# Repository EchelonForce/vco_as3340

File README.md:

# Eurorack VCO AS3340

This is a design for a eurorack VCO using the AS3340 VCO chip.

Full writeup here: https://www.robotdialogs.com/2023/02/eurorack-vco-module-as3340-v21.html
v1. writeup: https://www.robotdialogs.com/2022/09/eurorack-vco-module-as3340.html

This work is licensed under a Creative Commons Attribution-NonCommercial-ShareAlike 4.0 International License. https://creativecommons.org/licenses/by-nc-sa/4.0/

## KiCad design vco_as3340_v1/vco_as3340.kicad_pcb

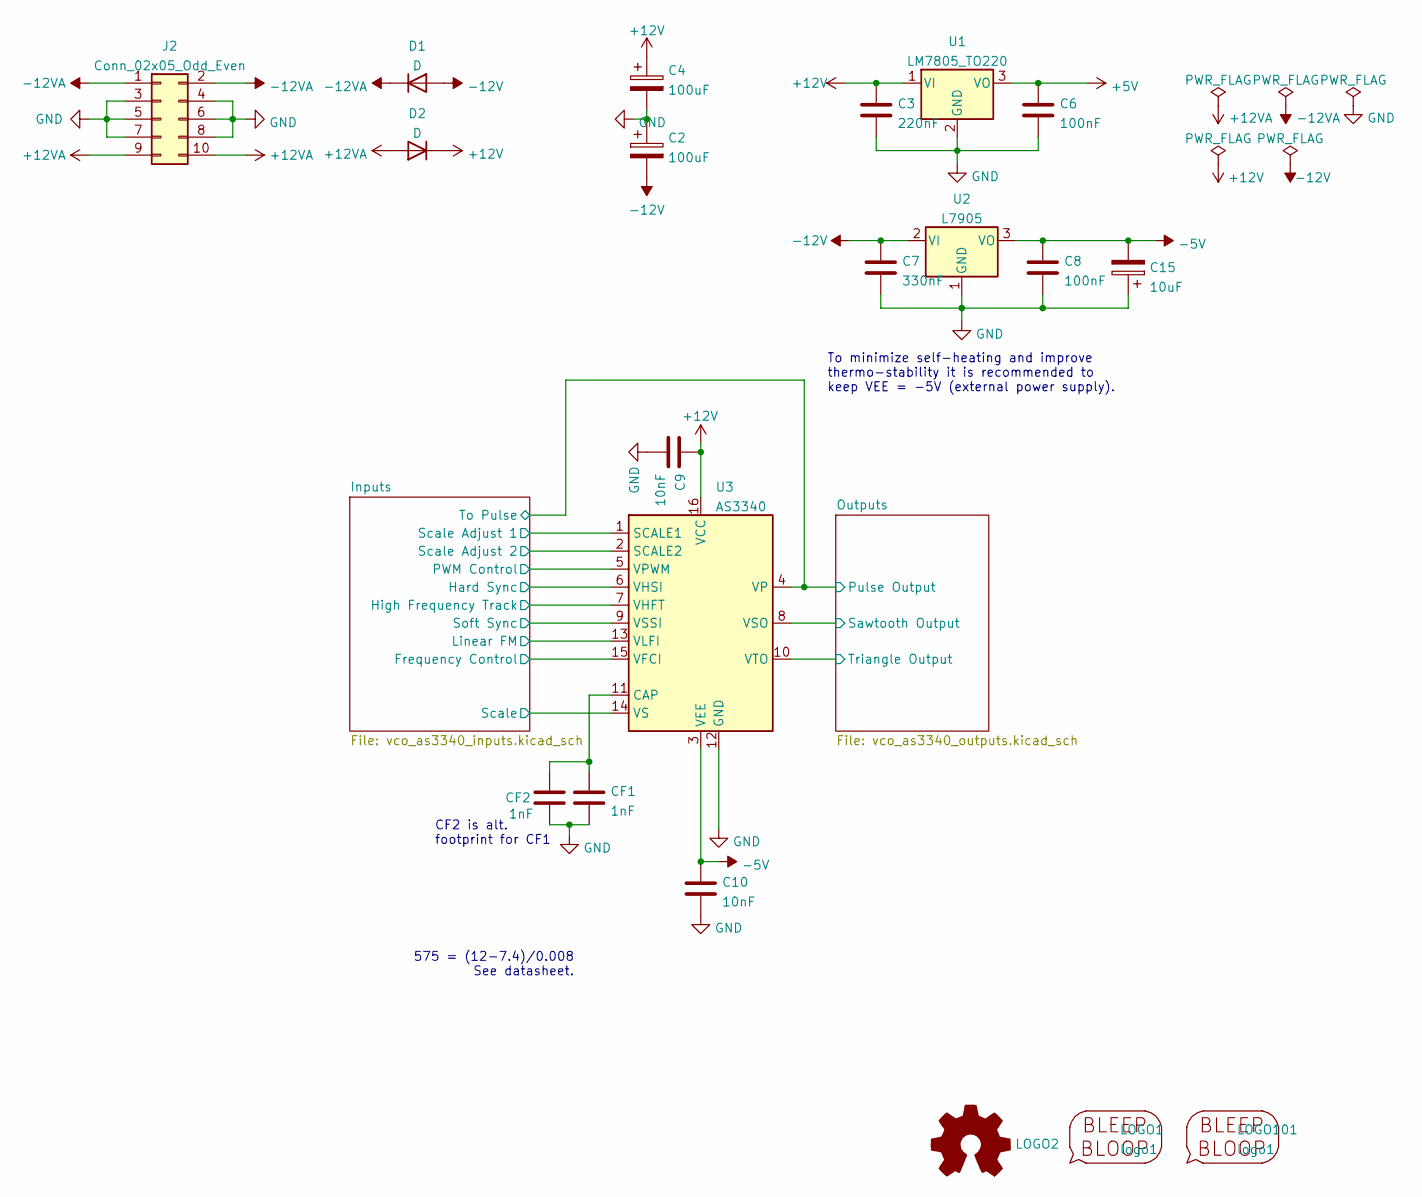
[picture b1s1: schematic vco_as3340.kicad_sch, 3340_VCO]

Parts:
C2, C4: 100uF; CP_Radial_D5.0mm_P2.50mm
C3: 220nF; C_1206_3216Metric_Pad1.33x1.80mm_HandSolder
C6, C8: 100nF; C_1206_3216Metric_Pad1.33x1.80mm_HandSolder
C7: 330nF; C_1206_3216Metric_Pad1.33x1.80mm_HandSolder
C9, C10: 10nF; C_1206_3216Metric_Pad1.33x1.80mm_HandSolder
C15: 10uF; CP_Radial_D5.0mm_P2.50mm
CF1: 1nF; C_Rect_L10.0mm_W2.5mm_P7.50mm_MKS4
CF2: 1nF; C_Rect_L7.0mm_W2.5mm_P5.00mm
D1, D2: D; D_A-405_P2.54mm_Vertical_KathodeUp
J2: Conn_02x05_Odd_Even; IDC-Header_2x05_P2.54mm_Vertical
LOGO1: logo1; Logo1
LOGO2: Logo_Open_Hardware_Small; OSHW-Symbol_6.7x6mm_SilkScreen
LOGO101: logo1; Logo2
U1: LM7805_TO220; TO-220-3_Vertical
U2: L7905; TO-220-3_Vertical
U3: AS3340; DIP-16_W7.62mm_Socket_LongPads

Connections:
+5V: C6.1, U1.3 (VO); also elsewhere on the board
+12V: C3.1, C4.1, C9.1, D2.1 (K), U1.1 (VI), U3.16 (VCC); also elsewhere on the board
+12VA: D2.2 (A), J2.9, J2.10
-5V: C8.1, C10.1, C15.2, U2.3 (VO), U3.3 (VEE); also elsewhere on the board
-12V: C2.2, C7.1, D1.2 (A), U2.2 (VI); also elsewhere on the board
-12VA: D1.1 (K), J2.1, J2.2
/Inputs/Frequency Control: U3.15 (VFCI); also elsewhere on the board
/Inputs/Hard Sync: U3.6 (VHSI); also elsewhere on the board
/Inputs/High Frequency Track: U3.7 (VHFT); also elsewhere on the board
/Inputs/Linear FM: U3.13 (VLFI); also elsewhere on the board
/Inputs/PWM Control: U3.5 (VPWM); also elsewhere on the board
/Inputs/Scale: U3.14 (VS); also elsewhere on the board
/Inputs/Scale Adjust 1: U3.1 (SCALE1); also elsewhere on the board
/Inputs/Scale Adjust 2: U3.2 (SCALE2); also elsewhere on the board
/Inputs/Soft Sync: U3.9 (VSSI); also elsewhere on the board
/Inputs/To Pulse: U3.4 (VP); also elsewhere on the board
/Outputs/Sawtooth Output: U3.8 (VSO); also elsewhere on the board
/Outputs/Triangle Output: U3.10 (VTO); also elsewhere on the board
GND: C2.1, C3.2, C4.2, C6.2, C7.2, C8.2, C9.2, C10.2, C15.1, CF1.2, CF2.2, J2.3, J2.4, J2.5, J2.6, J2.7, J2.8, U1.2 (GND), U2.1 (GND), U3.12 (GND); also elsewhere on the board
unnamed: CF1.1, CF2.1, U3.11 (CAP)

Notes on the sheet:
575 = (12-7.4)/0.008 See datasheet.
To minimize self-heating and improve thermo-stability it is recommended to keep VEE = -5V (external power supply).
CF2 is alt. footprint for CF1

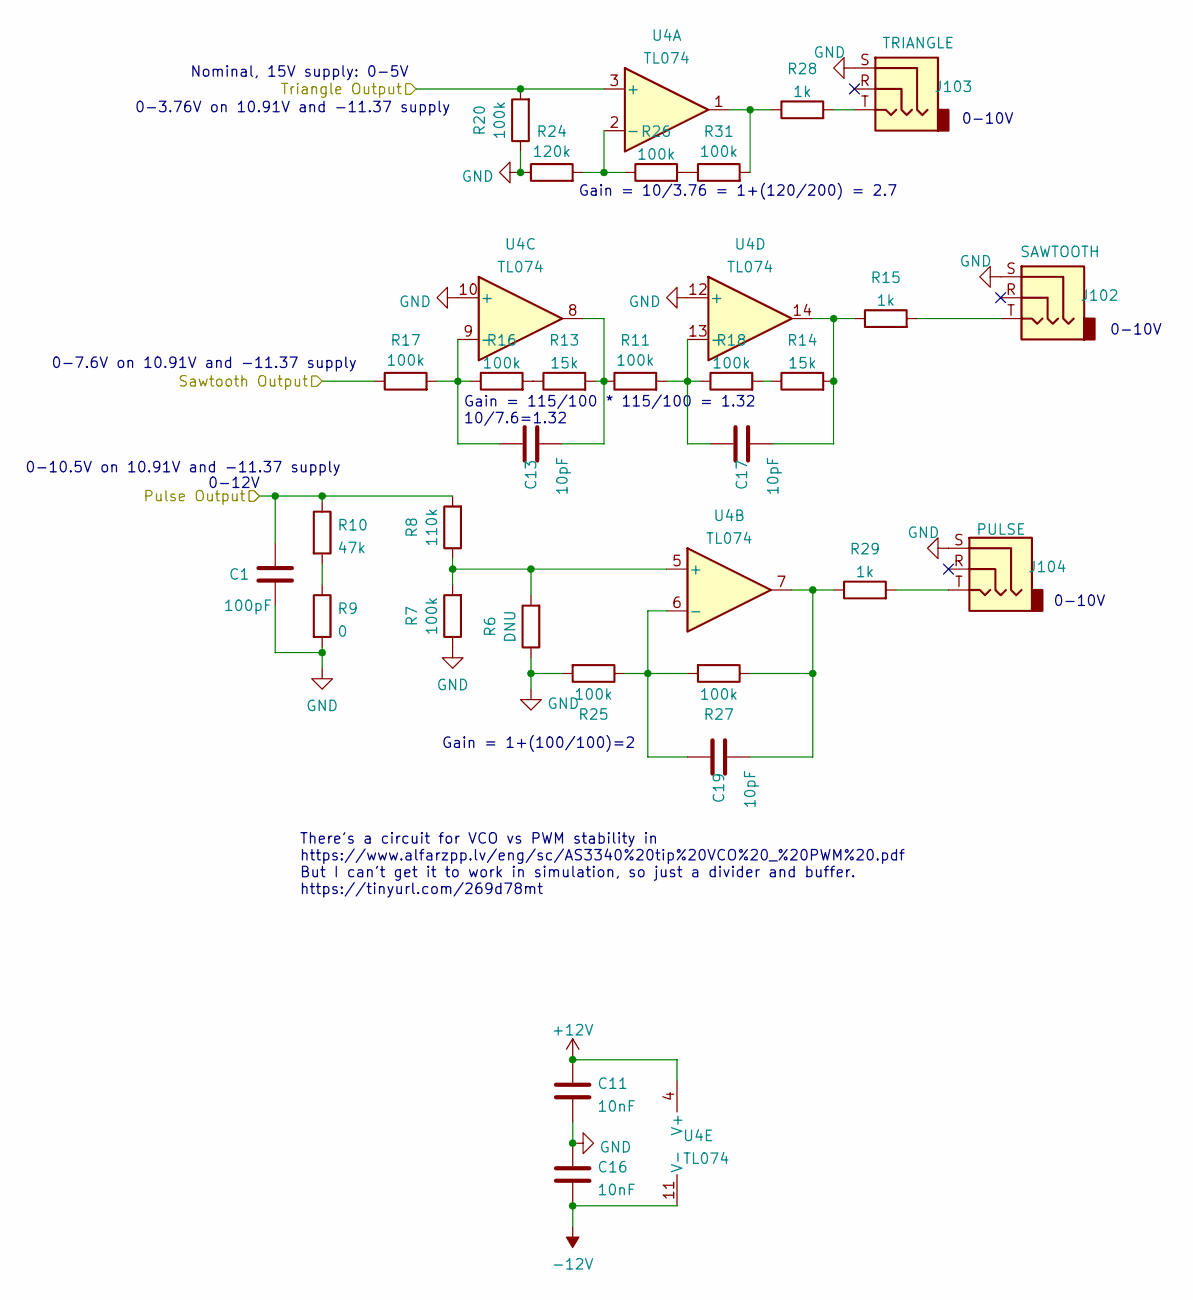
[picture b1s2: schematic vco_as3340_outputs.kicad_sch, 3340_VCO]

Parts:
C1: 100pF; C_1206_3216Metric_Pad1.33x1.80mm_HandSolder
C11, C16: 10nF; C_1206_3216Metric_Pad1.33x1.80mm_HandSolder
C13, C17, C19: 10pF; C_1206_3216Metric_Pad1.33x1.80mm_HandSolder
J102: SAWTOOTH; Jack_3.5mm_MJ-355W_Vertical
J103: TRIANGLE; Jack_3.5mm_MJ-355W_Vertical
J104: PULSE; Jack_3.5mm_MJ-355W_Vertical
R6: DNU; R_1206_3216Metric_Pad1.30x1.75mm_HandSolder
R7, R11, R16, R17, R18, R20, R25, R26, R27, R31: 100k; R_1206_3216Metric_Pad1.30x1.75mm_HandSolder
R8: 110k; R_1206_3216Metric_Pad1.30x1.75mm_HandSolder
R9: 0; R_1206_3216Metric_Pad1.30x1.75mm_HandSolder
R10: 47k; R_1206_3216Metric_Pad1.30x1.75mm_HandSolder
R13, R14: 15k; R_1206_3216Metric_Pad1.30x1.75mm_HandSolder
R15, R28, R29: 1k; R_1206_3216Metric_Pad1.30x1.75mm_HandSolder
R24: 120k; R_1206_3216Metric_Pad1.30x1.75mm_HandSolder
U4: TL074; DIP-14_W7.62mm_Socket_LongPads

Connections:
+12V: C11.1, U4.4 (V+); also elsewhere on the board
-12V: C16.2, U4.11 (V-); also elsewhere on the board
/Inputs/To Pulse: C1.1, R8.2, R10.1; also elsewhere on the board
/Outputs/Sawtooth Output: R17.1; also elsewhere on the board
/Outputs/Triangle Output: R20.2, U4.3 (+); also elsewhere on the board
GND: C1.2, C11.2, C16.1, J102.S, J103.S, J104.S, R6.1, R7.1, R9.2, R20.1, R24.1, R25.2, U4.10 (+), U4.12 (+); also elsewhere on the board
unnamed: C13.1, R16.1, R17.2, U4.9 (-)
unnamed: C13.2, R11.1, R13.2, U4.8
unnamed: C17.1, R11.2, R18.1, U4.13 (-)
unnamed: C17.2, R14.2, R15.1, U4.14
unnamed: C19.1, R25.1, R27.2, U4.6 (-)
unnamed: C19.2, R27.1, R29.1, U4.7
unnamed: J102.T, R15.2
unnamed: J103.T, R28.2
unnamed: J104.T, R29.2
unnamed: R6.2, R7.2, R8.1, U4.5 (+)
unnamed: R9.1, R10.2
unnamed: R13.1, R16.2
unnamed: R14.1, R18.2
unnamed: R24.2, R26.1, U4.2 (-)
unnamed: R26.2, R31.1
unnamed: R28.1, R31.2, U4.1

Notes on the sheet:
0-10.5V on 10.91V and -11.37 supply
0-10V
Gain = 1+(100/100)=2
0-12V
0-7.6V on 10.91V and -11.37 supply
There's a circuit for VCO vs PWM stability in https://www.alfarzpp.lv/eng/sc/AS3340%20tip%20VCO%20_%20PWM%20.pdf But I can't get it to work in simulation, so just a divider and buffer. https://tinyurl.com/269d78mt
Gain = 10/3.76 = 1+(120/200) = 2.7
Gain = 115/100 * 115/100 = 1.32 10/7.6=1.32
Nominal, 15V supply: 0-5V
0-3.76V on 10.91V and -11.37 supply

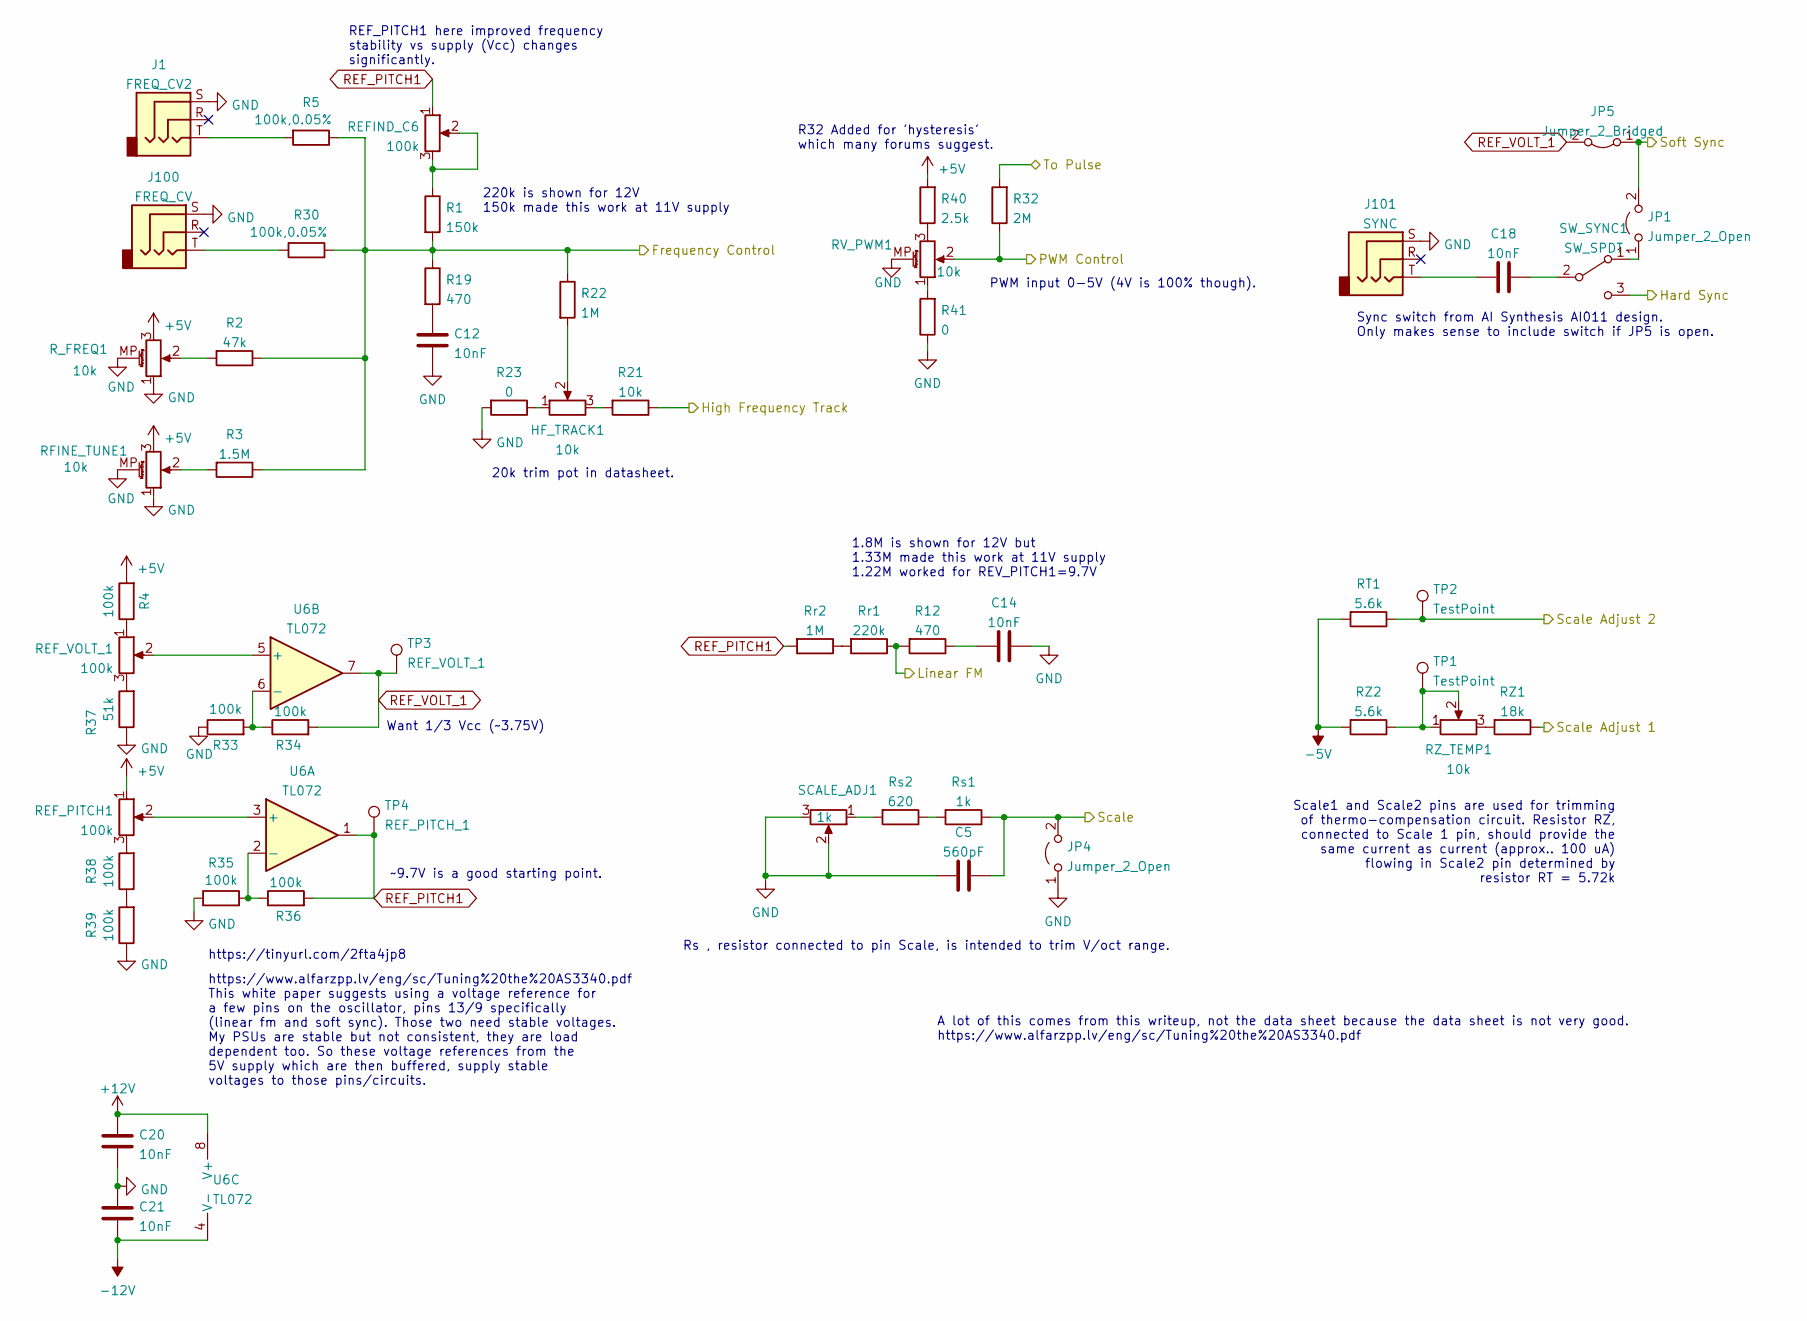
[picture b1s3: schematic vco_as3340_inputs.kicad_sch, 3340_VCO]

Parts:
C5: 560pF; C_1206_3216Metric_Pad1.33x1.80mm_HandSolder
C12, C14, C18, C20, C21: 10nF; C_1206_3216Metric_Pad1.33x1.80mm_HandSolder
HF_TRACK1: 10k; Potentiometer_Bourns_3296W_Vertical
J1: FREQ_CV2; Jack_3.5mm_MJ-355W_Vertical
J100: FREQ_CV; Jack_3.5mm_MJ-355W_Vertical
J101: SYNC; Jack_3.5mm_MJ-355W_Vertical
JP1: Jumper_2_Open; SolderJumper-2_P1.3mm_Open_Pad1.0x1.5mm
JP4: Jumper_2_Open; PinHeader_1x02_P2.54mm_Vertical
JP5: Jumper_2_Bridged; SolderJumper-2_P1.3mm_Bridged_Pad1.0x1.5mm
R1: 150k; R_1206_3216Metric_Pad1.30x1.75mm_HandSolder
R2: 47k; R_1206_3216Metric_Pad1.30x1.75mm_HandSolder
R3: 1.5M; R_1206_3216Metric_Pad1.30x1.75mm_HandSolder
R4, R33, R34, R35, R36, R38, R39: 100k; R_1206_3216Metric_Pad1.30x1.75mm_HandSolder
R5, R30: 100k,0.05%; R_1206_3216Metric_Pad1.30x1.75mm_HandSolder
R12, R19: 470; R_1206_3216Metric_Pad1.30x1.75mm_HandSolder
R21: 10k; R_1206_3216Metric_Pad1.30x1.75mm_HandSolder
R22: 1M; R_1206_3216Metric_Pad1.30x1.75mm_HandSolder
R23, R41: 0; R_1206_3216Metric_Pad1.30x1.75mm_HandSolder
R32: 2M; R_1206_3216Metric_Pad1.30x1.75mm_HandSolder
R37: 51k; R_1206_3216Metric_Pad1.30x1.75mm_HandSolder
R40: 2.5k; R_1206_3216Metric_Pad1.30x1.75mm_HandSolder
REFIND_C6: 100k; Potentiometer_Bourns_3296W_Vertical
REF_PITCH1: 100k; Potentiometer_Bourns_3296W_Vertical
REF_VOLT_1: 100k; Potentiometer_Bourns_3296W_Vertical
RFINE_TUNE1: 10k; Potentiometer_Alpha_RD901F-40-00D_Single_Vertical_w_3d
RT1: 5.6k; R_1206_3216Metric_Pad1.30x1.75mm_HandSolder
RV_PWM1: 10k; Potentiometer_Alpha_RD901F-40-00D_Single_Vertical_w_3d
RZ1: 18k; R_1206_3216Metric_Pad1.30x1.75mm_HandSolder
RZ2: 5.6k; R_1206_3216Metric_Pad1.30x1.75mm_HandSolder
RZ_TEMP1: 10k; Potentiometer_Bourns_3296W_Vertical
R_FREQ1: 10k; Potentiometer_Alpha_RD901F-40-00D_Single_Vertical_w_3d
Rr1: 220k; R_1206_3216Metric_Pad1.30x1.75mm_HandSolder
Rr2: 1M; R_1206_3216Metric_Pad1.30x1.75mm_HandSolder
Rs1: 1k; R_1206_3216Metric_Pad1.30x1.75mm_HandSolder
Rs2: 620; R_1206_3216Metric_Pad1.30x1.75mm_HandSolder
SCALE_ADJ1: 1k; Potentiometer_Bourns_3296W_Vertical
SW_SYNC1: SW_SPDT; SPDT_Toggle
TP1, TP2: TestPoint; PinHeader_1x01_P2.54mm_Vertical
TP3: REF_VOLT_1; PinHeader_1x01_P2.54mm_Vertical
TP4: REF_PITCH_1; PinHeader_1x01_P2.54mm_Vertical
U6: TL072; DIP-8_W7.62mm_Socket_LongPads

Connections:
+5V: R4.2, R40.2, REF_PITCH1.1, RFINE_TUNE1.3, R_FREQ1.3; also elsewhere on the board
+12V: C20.1, U6.8 (V+); also elsewhere on the board
-5V: RT1.2, RZ2.2; also elsewhere on the board
-12V: C21.2, U6.4 (V-); also elsewhere on the board
/Inputs/Frequency Control: R1.2, R2.1, R3.1, R5.1, R19.1, R22.1, R30.1; also elsewhere on the board
/Inputs/Hard Sync: SW_SYNC1.3 (C); also elsewhere on the board
/Inputs/High Frequency Track: R21.1; also elsewhere on the board
/Inputs/Linear FM: R12.2, Rr1.1; also elsewhere on the board
/Inputs/PWM Control: R32.1, RV_PWM1.2; also elsewhere on the board
/Inputs/Scale: C5.2, JP4.2 (B), Rs1.1; also elsewhere on the board
/Inputs/Scale Adjust 1: RZ1.1; also elsewhere on the board
/Inputs/Scale Adjust 2: RT1.1, TP2.1; also elsewhere on the board
/Inputs/Soft Sync: JP1.2 (B), JP5.1 (A); also elsewhere on the board
/Inputs/To Pulse: R32.2; also elsewhere on the board
GND: C5.1, C12.1, C14.2, C20.2, C21.1, J1.S, J100.S, J101.S, JP4.1 (A), R23.2, R33.1, R35.1, R37.1, R39.1, R41.1, RFINE_TUNE1.1, RFINE_TUNE1.MP (MountPin), RV_PWM1.MP (MountPin), R_FREQ1.1, R_FREQ1.MP (MountPin), SCALE_ADJ1.2, SCALE_ADJ1.3; also elsewhere on the board
unnamed: C12.2, R19.2
unnamed: C14.1, R12.1
unnamed: C18.1, J101.T
unnamed: C18.2, SW_SYNC1.2 (B)
unnamed: HF_TRACK1.1, R23.1
unnamed: HF_TRACK1.2, R22.2
unnamed: HF_TRACK1.3, R21.2
unnamed: J1.T, R5.2
unnamed: J100.T, R30.2
unnamed: R1.1, REFIND_C6.2, REFIND_C6.3
unnamed: R2.2, R_FREQ1.2
unnamed: R3.2, RFINE_TUNE1.2
unnamed: R4.1, REF_VOLT_1.1
unnamed: R33.2, R34.1, U6.6 (-)
unnamed: R35.2, R36.1, U6.2 (-)
unnamed: R37.2, REF_VOLT_1.3
unnamed: R38.1, R39.2
unnamed: R38.2, REF_PITCH1.3
unnamed: R40.1, RV_PWM1.3
unnamed: R41.2, RV_PWM1.1
unnamed: REF_PITCH1.2, U6.3 (+)
unnamed: REF_VOLT_1.2, U6.5 (+)
unnamed: RZ1.2, RZ_TEMP1.3
unnamed: RZ2.1, RZ_TEMP1.1, RZ_TEMP1.2, TP1.1
unnamed: Rr1.2, Rr2.1
unnamed: Rs1.2, Rs2.1
unnamed: Rs2.2, SCALE_ADJ1.1
unnamed: JP1.1 (A), SW_SYNC1.1 (A)
REF_PITCH1: R36.2, REFIND_C6.1, Rr2.2, TP4.1, U6.1
REF_VOLT_1: JP5.2 (B), R34.2, TP3.1, U6.7

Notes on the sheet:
R32 Added for 'hysteresis' which many forums suggest.
Scale1 and Scale2 pins are used for trimming of thermo-compensation circuit. Resistor RZ, connected to Scale 1 pin, should provide the same current as current (approx.. 100 uA) flowing in Scale2 pin determined by resistor RT = 5.72k
PWM input 0-5V (4V is 100% though).
220k is shown for 12V 150k made this work at 11V supply
REF_PITCH1 here improved frequency stability vs supply (Vcc) changes significantly.
~9.7V is a good starting point.
https://www.alfarzpp.lv/eng/sc/Tuning%20the%20AS3340.pdf This white paper suggests using a voltage reference for a few pins on the oscillator, pins 13/9 specifically (linear fm and soft sync). Those two need stable voltages. My PSUs are stable but not consistent, they are load dependent too. So the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
Sync switch from AI Synthesis AI011 design. Only makes sense to include switch if JP5 is open.
20k trim pot in datasheet.
Rs , resistor connected to pin Scale, is intended to trim V/oct range.
https://tinyurl.com/2fta4jp8
1.8M is shown for 12V but 1.33M made this work at 11V supply 1.22M worked for REV_PITCH1=9.7V
Want 1/3 Vcc (~3.75V)
A lot of this comes from this writeup, not the data sheet because the data sheet is not very good. https://www.alfarzpp.lv/eng/sc/Tuning%20the%20AS3340.pdf

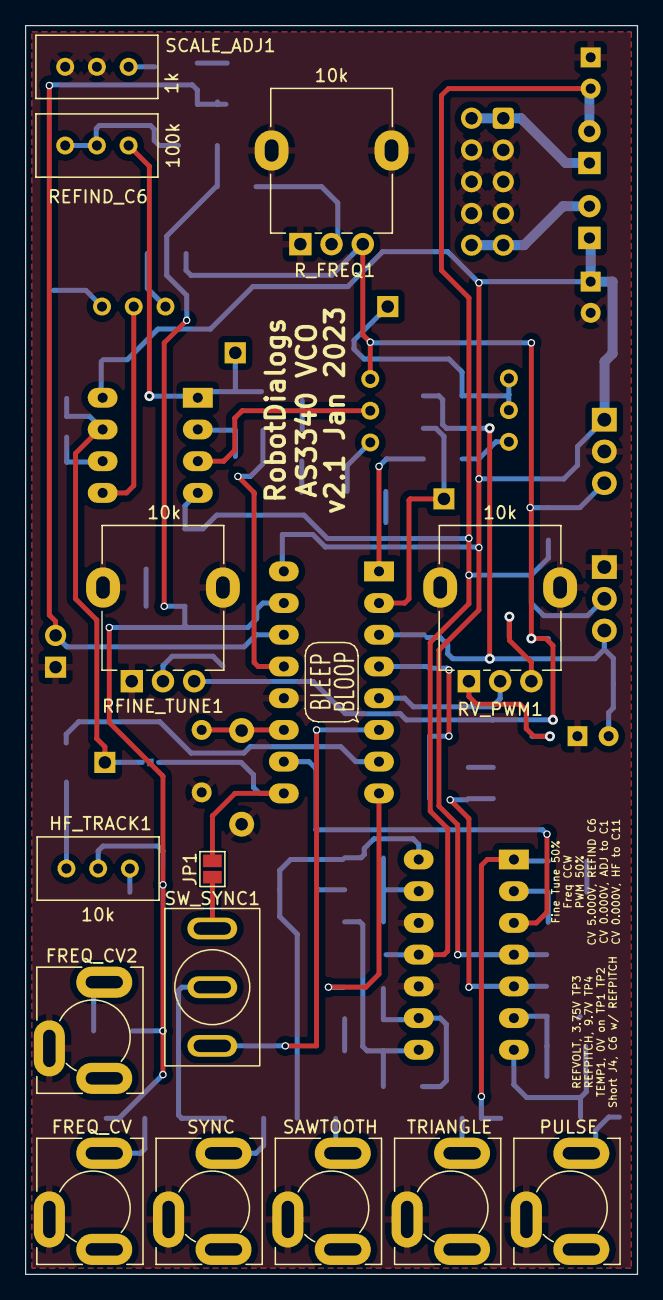
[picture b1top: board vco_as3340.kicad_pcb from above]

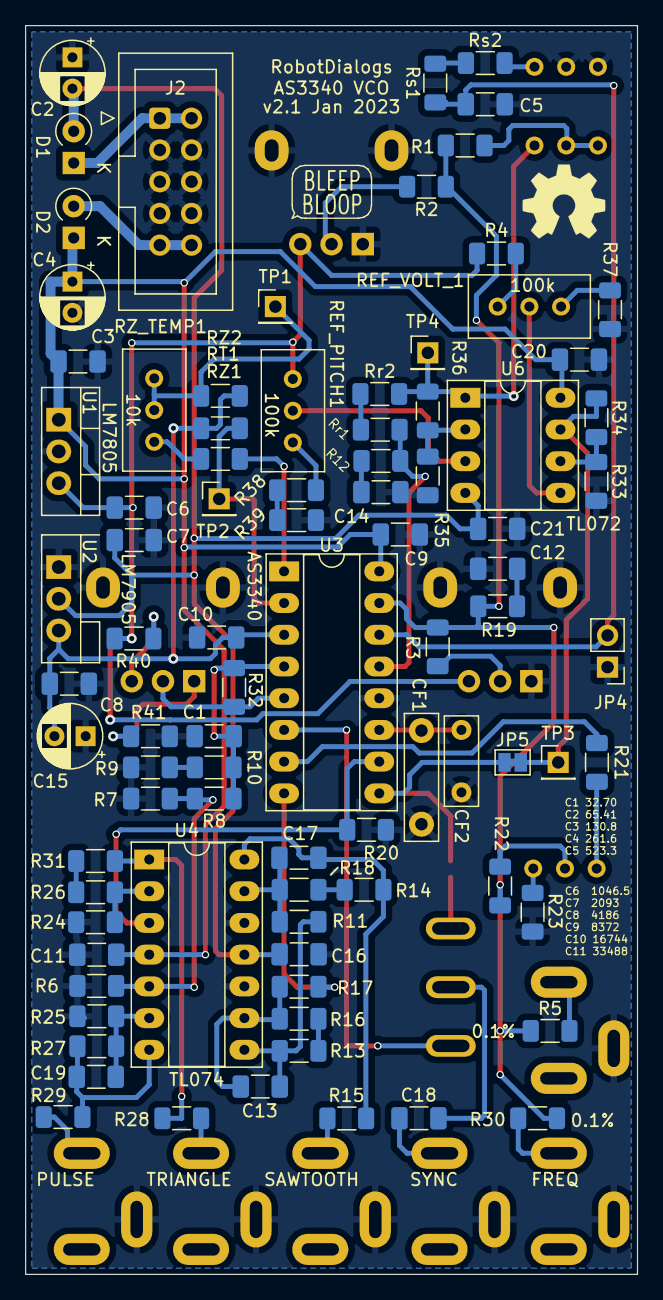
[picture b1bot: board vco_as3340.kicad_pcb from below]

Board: 2 copper layers, 49.0 x 100.0 mm, 105 parts (89 on the bottom side), 66 nets.

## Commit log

2022-07-02 Initial Commit .gitignore
2022-07-02 First pass at a schematic, untested.
    https://www.alfarzpp.lv/eng/sc/AS3340.pdf
    https://www.alfarzpp.lv/eng/sc/Tuning%20the%20AS3340.pdf
2022-07-03 Schematic update from breadboarding, start layout
2022-07-04 Layout and routing done
2022-07-04 Geographic re-annotate and cleanup
2022-07-07 Grid origin update
2022-07-27 Add Notes.txt
2022-07-27 Panelized v1 and bom
2022-07-27 Front Panel v1 CAD
2022-07-27 Front Panel v1.1
    Moved engraved text around
2022-09-10 front panel files, renders, pdfs
2022-09-10 Testing notes
2022-09-10 Add readme
2022-10-16 Schematic Changes v1 to v2
    - R10 = 47k
    - R9 = 0ohm
    - New C1 100pF across R10 and R9
    - New C15 10uF polarized cap from -5 to GND.
    - R6 DNU
    - R21 & R23 changed to 5.1k
2022-12-09 v2 re-layout pcb
2022-12-10 Routing done
2022-12-17 v2 panelized
2022-12-17 Rename kicad project
2023-01-09 Add Front Panel v2 docs
2023-01-09 Additional pdfs of v1 and v2
2023-01-09 V2 Test Notes and redline
2023-01-10 Changes to v2 from testing
2023-01-10 v2.1 panelized
2023-01-19 Add v2.1 schematic pdf
    Adjusted R40 to be 2.4k instead of 2.5k which isn't an E24 value.
2023-01-19 Front Panel v2.1
    Removed trim pot holes that were in the wrong place and not labeled,
    don't really need them.
    Removed the SYNC switch, see schematic notes on v2 & v2.1, it doesn't
    add much.
2023-02-18 Update links in README
